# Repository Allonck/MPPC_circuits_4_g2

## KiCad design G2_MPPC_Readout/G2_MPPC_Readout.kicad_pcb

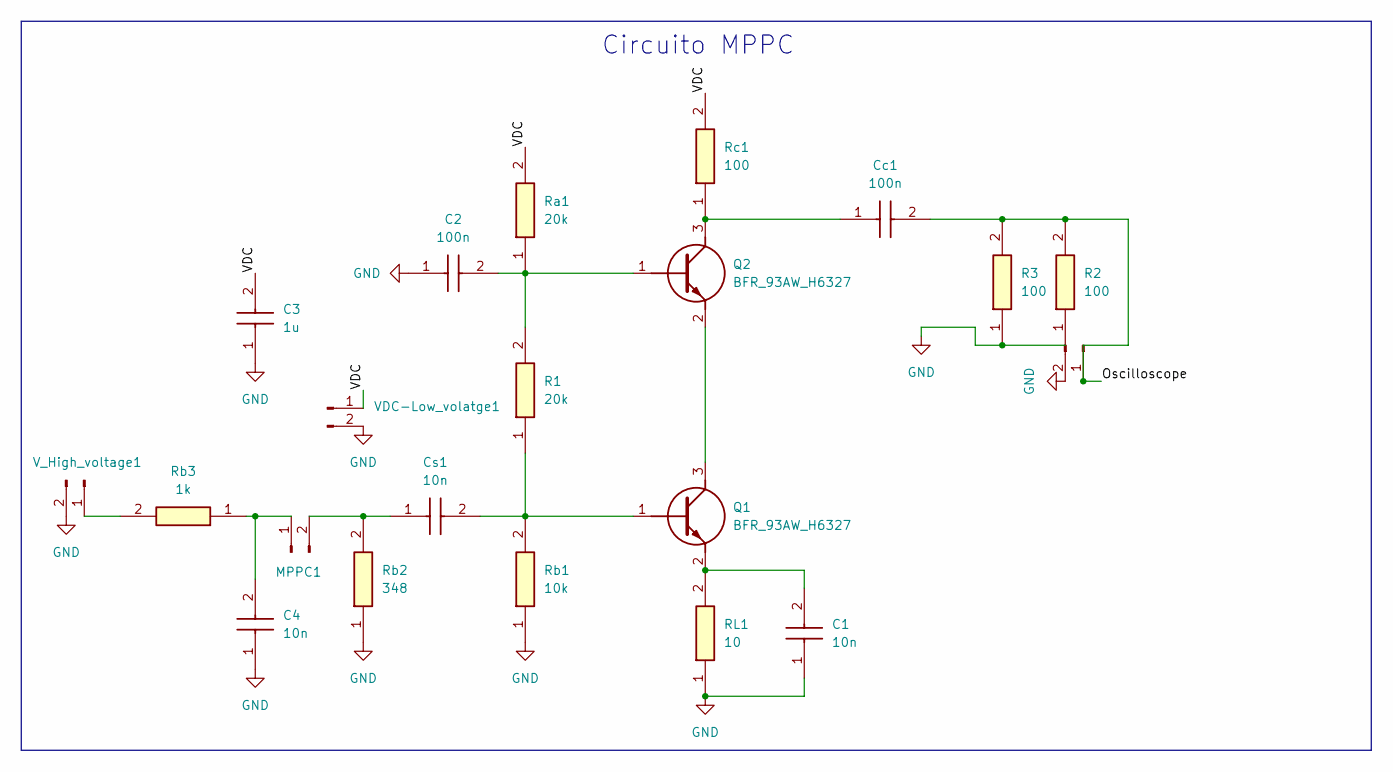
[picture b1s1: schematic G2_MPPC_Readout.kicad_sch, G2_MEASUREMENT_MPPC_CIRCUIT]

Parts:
C1, C4: 10n; C_0805_2012Metric; Mouser Part Number 710-885342208021
C2: 100n; C_0805_2012Metric; Mouser Part Number 710-885342208021
C3: 1u; C_0805_2012Metric; Mouser Part Number 710-885342208021
Cc1: 100n; C_0805_2012Metric; Mouser Part Number 710-885342208021
Cs1: 10n; C_0805_2012Metric; Mouser Part Number 710-885342208021
MPPC1: Conn_01x02_Pin; PinHeader_1x02_P2.54mm_Vertical
Oscilloscope1: Conn_01x02_Pin; PinHeader_1x02_P2.54mm_Vertical
Q1, Q2: BFR_93AW_H6327; SOT-23; Mouser Part Number 726-BFR93AWH6327
R1: 20k; R_1206_3216Metric; Mouser Part Number 603-RC1206FR-SKE96L
R2, R3: 100; R_1206_3216Metric; Mouser Part Number 603-RC1206FR-SKE96L
RL1: 10; R_1206_3216Metric; Mouser Part Number 603-RC1206FR-SKE96L
Ra1: 20k; R_1206_3216Metric; Mouser Part Number 603-RC1206FR-SKE96L
Rb1: 10k; R_1206_3216Metric; Mouser Part Number 603-RC1206FR-SKE96L
Rb2: 348; R_1206_3216Metric; Mouser Part Number 603-RC1206FR-SKE96L
Rb3: 1k; R_1206_3216Metric; Mouser Part Number 603-RC1206FR-SKE96L
Rc1: 100; R_1206_3216Metric; Mouser Part Number 603-RC1206FR-SKE96L
VDC-Low_volatge1: Conn_01x02_Pin; PinHeader_1x02_P2.54mm_Vertical
V_High_voltage1: Conn_01x02_Pin; PinHeader_1x02_P2.54mm_Vertical

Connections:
/Oscilloscope: Cc1.2, Oscilloscope1.1, R2.2, R3.2
/VDC: C3.2, Ra1.2, Rc1.2, VDC-Low_volatge1.1
GND: C1.1, C2.1, C3.1, C4.1, Oscilloscope1.2, R2.1, R3.1, RL1.1, Rb1.1, Rb2.1, VDC-Low_volatge1.2, V_High_voltage1.2
unnamed: C4.2, MPPC1.1, Rb3.1
unnamed: Cs1.1, MPPC1.2, Rb2.2
unnamed: Cs1.2, Q1.1 (B), R1.1, Rb1.2
unnamed: Q1.3 (C), Q2.2 (E)
unnamed: C1.2, Q1.2 (E), RL1.2
unnamed: C2.2, Q2.1 (B), R1.2, Ra1.1
unnamed: Cc1.1, Q2.3 (C), Rc1.1
unnamed: Rb3.2, V_High_voltage1.1

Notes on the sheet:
Circuito MPPC

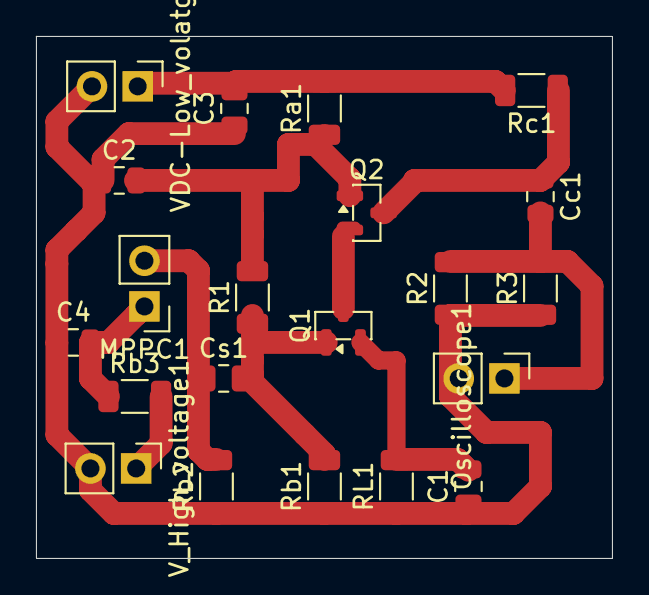
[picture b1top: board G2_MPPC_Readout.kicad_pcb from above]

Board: 2 copper layers, 32.0 x 29.0 mm, 21 parts (0 on the bottom side), 11 nets.
